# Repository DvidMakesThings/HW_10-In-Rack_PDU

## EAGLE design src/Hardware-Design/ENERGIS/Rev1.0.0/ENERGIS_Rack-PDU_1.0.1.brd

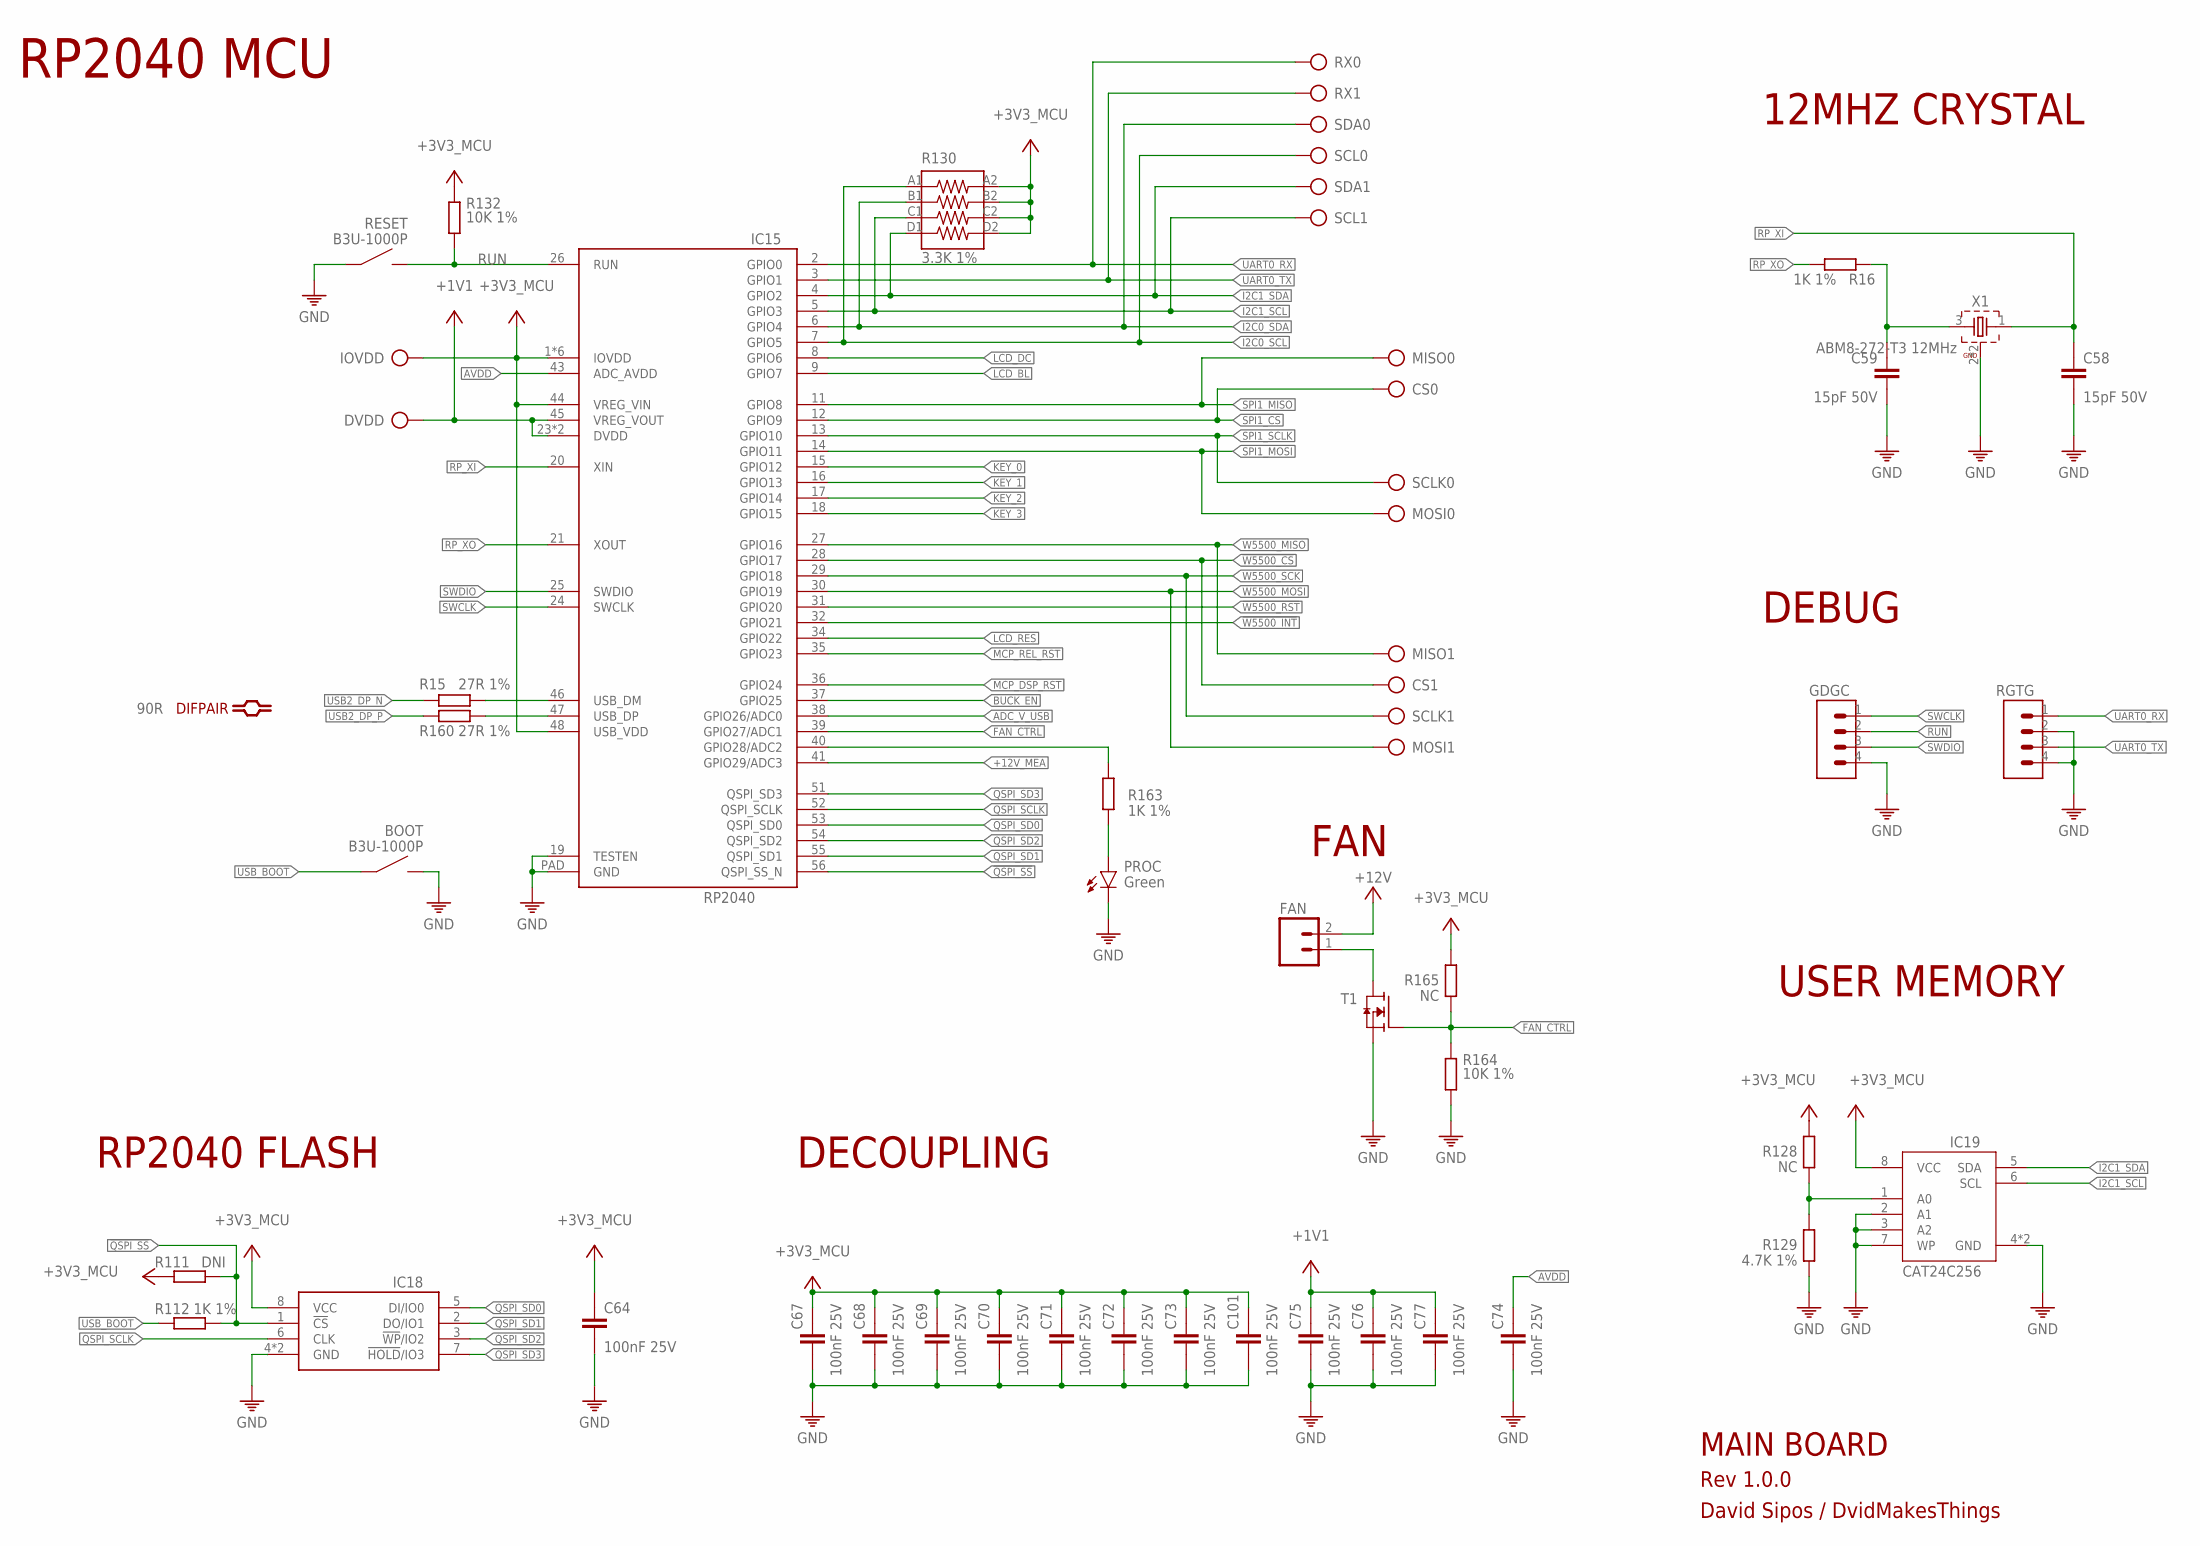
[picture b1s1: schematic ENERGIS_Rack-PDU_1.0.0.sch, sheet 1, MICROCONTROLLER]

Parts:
BOOT: B3U-1000P
C58, C59: 15pF 50V; 0201
C64, C67, C68, C69, C70, C71, C72, C73, C74, C75, C76, C77, C101: 100nF 25V; 0201
CS0, CS1: TP
DVDD: TP
FAN: M02; 02P
GDGC: CON-1X4; 1X4
IC15: RP2040; QFN56
IC18: W25Q128JVPIQ; SON127P600X500X75-8N
IC19: CAT24C256HU4IGT3; SON50P300X200X50-9T130X140N
IOVDD: TP
MISO0, MISO1: TP
MOSI0, MOSI1: TP
PROC: Green; LED-0603
R15, R160: 27R 1%; 0201
R16: 1K 1%; 0201
R111: DNI; R0201
R112, R163: 1K 1%; 0402
R128, R165: NC; R0201
R129: 4.7K 1%; 0201
R130: 3.3K 1%; _0603X4-1206
R132, R164: 10K 1%; 0402
RESET: B3U-1000P
RGTG: CON-1X4; 1X4
RX0, RX1: TP
SCL0, SCL1: TP
SCLK0, SCLK1: TP
SDA0, SDA1: TP
T1: BSS138; SOT23
X1: ABM8-272-T3 12MHz; WE-XTAL_CFPX-180

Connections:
!QSPI_SS: IC15.56 (QSPI_SS_N), IC18.1 (!CS), R111.1, R112.2
!W5500_CS: CS1.TP, IC15.28 (GPIO17); also elsewhere on the board
!W5500_INT: IC15.32 (GPIO21); also elsewhere on the board
!W5500_RST: IC15.31 (GPIO20); also elsewhere on the board
+1V1: C75.1, C76.1, C77.1, DVDD.TP, IC15.23 (DVDD), IC15.45 (VREG_VOUT), IC15.50 (DVDD)
+3V3_MCU: C64.1, C67.1, C68.1, C69.1, C70.1, C71.1, C72.1, C73.1, C101.1, IC15.1 (IOVDD), IC15.10 (IOVDD), IC15.22 (IOVDD), IC15.33 (IOVDD), IC15.42 (IOVDD), IC15.44 (VREG_VIN), IC15.48 (USB_VDD), IC15.49 (IOVDD), IC18.8 (VCC), IC19.8 (VCC), IOVDD.TP, R111.2, R128.2, R130.A2 (8), R130.B2 (7), R130.C2 (6), R130.D2 (5), R132.1, R165.2; also elsewhere on the board
+12V: FAN.2; also elsewhere on the board
+12V_MEA: IC15.41 (GPIO29/ADC3); also elsewhere on the board
ADC_V_USB: IC15.38 (GPIO26/ADC0); also elsewhere on the board
AVDD: C74.1, IC15.43 (ADC_AVDD); also elsewhere on the board
BUCK_EN: IC15.37 (GPIO25); also elsewhere on the board
FAN_CTRL: IC15.39 (GPIO27/ADC1), R164.1, R165.1, T1.1 (G)
GND: BOOT.2, C58.2, C59.2, C64.2, C67.2, C68.2, C69.2, C70.2, C71.2, C72.2, C73.2, C74.2, C75.2, C76.2, C77.2, C101.2, GDGC.4, IC15.19 (TESTEN), IC15.PAD (GND), IC18.4 (GND), IC18.PAD (GND), IC19.2 (A1), IC19.3 (A2), IC19.4 (GND), IC19.7 (WP), IC19.9 (GND), PROC.C, R129.1, R164.2, RESET.1, RGTG.2, RGTG.4, T1.2 (S), X1.2 (GND), X1.4 (GND); also elsewhere on the board
I2C0_SCL: IC15.7 (GPIO5), R130.A1 (1), SCL0.TP; also elsewhere on the board
I2C0_SDA: IC15.6 (GPIO4), R130.B1 (2), SDA0.TP; also elsewhere on the board
I2C1_SCL: IC15.5 (GPIO3), IC19.6 (SCL), R130.C1 (3), SCL1.TP; also elsewhere on the board
I2C1_SDA: IC15.4 (GPIO2), IC19.5 (SDA), R130.D1 (4), SDA1.TP; also elsewhere on the board
KEY_0: IC15.15 (GPIO12); also elsewhere on the board
KEY_1: IC15.16 (GPIO13); also elsewhere on the board
KEY_2: IC15.17 (GPIO14); also elsewhere on the board
KEY_3: IC15.18 (GPIO15); also elsewhere on the board
LCD_BL: IC15.9 (GPIO7); also elsewhere on the board
LCD_DC: IC15.8 (GPIO6); also elsewhere on the board
LCD_RES: IC15.34 (GPIO22); also elsewhere on the board
MCP_DSP_RST: IC15.36 (GPIO24); also elsewhere on the board
MCP_REL_RST: IC15.35 (GPIO23); also elsewhere on the board
unnamed: IC15.40 (GPIO28/ADC2), R163.2
unnamed: PROC.A, R163.1
unnamed: FAN.1, T1.3 (D)
unnamed: C59.1, R16.1, X1.3 (2)
unnamed: IC19.1 (A0), R128.1, R129.2
QSPI_SCLK: IC15.52 (QSPI_SCLK), IC18.6 (CLK)
QSPI_SD0: IC15.53 (QSPI_SD0), IC18.5 (DI/IO0)
QSPI_SD1: IC15.55 (QSPI_SD1), IC18.2 (DO/IO1)
QSPI_SD2: IC15.54 (QSPI_SD2), IC18.3 (!WP!/IO2)
QSPI_SD3: IC15.51 (QSPI_SD3), IC18.7 (!HOLD!/IO3)
RP_DP_N: IC15.46 (USB_DM), R15.2
RP_DP_P: IC15.47 (USB_DP), R160.2
RP_XI: C58.1, IC15.20 (XIN), X1.1
RP_XO: IC15.21 (XOUT), R16.2
RUN: GDGC.2, IC15.26 (RUN), R132.2, RESET.2
SPI1_CS: CS0.TP, IC15.12 (GPIO9); also elsewhere on the board
SPI1_MISO: IC15.11 (GPIO8), MISO0.TP; also elsewhere on the board
SPI1_MOSI: IC15.14 (GPIO11), MOSI0.TP; also elsewhere on the board
SPI1_SCLK: IC15.13 (GPIO10), SCLK0.TP; also elsewhere on the board
SWCLK: GDGC.1, IC15.24 (SWCLK)
SWDIO: GDGC.3, IC15.25 (SWDIO)
UART0_RX: IC15.2 (GPIO0), RGTG.1, RX0.TP; also elsewhere on the board
UART0_TX: IC15.3 (GPIO1), RGTG.3, RX1.TP; also elsewhere on the board
USB2_DP_N: R15.1; also elsewhere on the board
USB2_DP_P: R160.1; also elsewhere on the board
USB_BOOT: BOOT.1, R112.1
W5500_MISO: IC15.27 (GPIO16), MISO1.TP; also elsewhere on the board
W5500_MOSI: IC15.30 (GPIO19), MOSI1.TP; also elsewhere on the board
W5500_SCK: IC15.29 (GPIO18), SCLK1.TP; also elsewhere on the board

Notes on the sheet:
DECOUPLING
12MHZ CRYSTAL
RP2040 MCU
RP2040 FLASH
USER MEMORY
DEBUG
MAIN BOARD
Rev 1.0.0
David Sipos / DvidMakesThings
FAN

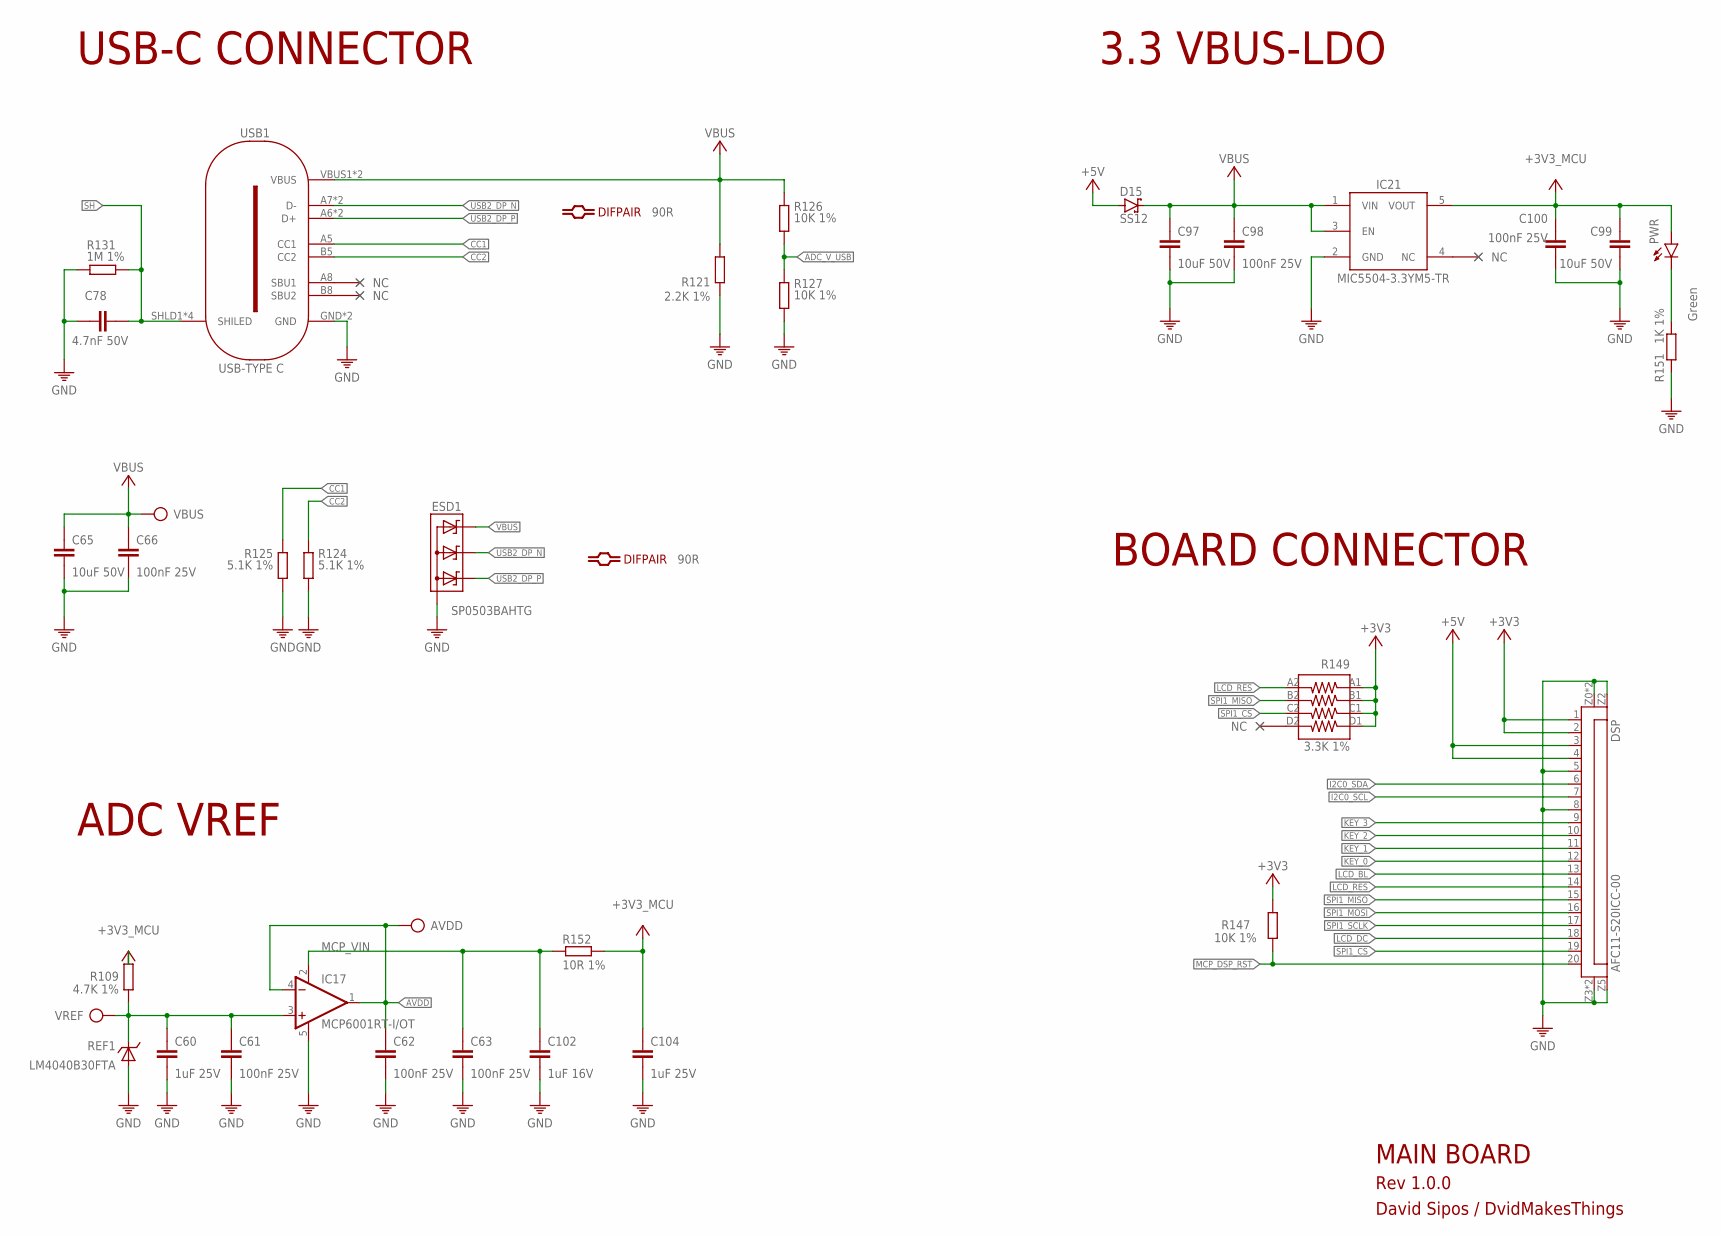
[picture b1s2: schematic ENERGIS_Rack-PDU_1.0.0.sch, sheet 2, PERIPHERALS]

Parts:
AVDD: TP
C60, C104: 1uF 25V; 0402
C61, C62, C63, C98, C100: 100nF 25V; 0201
C65, C97, C99: 10uF 50V; 0805
C66: 100nF 25V; 0402
C78: 4.7nF 50V; 0402
C102: 1uF 16V; 0201
D15: SS12; SMA/DO-214AC
DSP: AFC11-S20ICC-00; FPC20
ESD1: SP0503BAHTG; SOT143
IC17: MCP6001RT-I/OT; SOT23-5
IC21: MIC5504-3.3YM5; SOT23-5
PWR: Green; LED-0603
R109: 4.7K 1%; 0201
R121: 2.2K 1%; 0201
R124, R125: 5.1K 1%; 0201
R126, R127: 10K 1%; 0201
R131: 1M 1%; 0402
R147: 10K 1%; 0402
R149: 3.3K 1%; _0603X4-1206
R151: 1K 1%; 0402
R152: 10R 1%; 0201
REF1: LM4040B30FTA; SOT23
USB1: USB-TYPE-C-018; USB-C
VBUS: TP
VREF: TP

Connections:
+3V3: DSP.1, DSP.2, R147.2, R149.A1 (1), R149.B1 (2), R149.C1 (3), R149.D1 (4); also elsewhere on the board
+3V3_MCU: C99.1, C100.1, C104.1, IC21.5 (VOUT), PWR.A, R109.2, R152.1; also elsewhere on the board
+5V: D15.A, DSP.3, DSP.4; also elsewhere on the board
ADC_V_USB: R126.2, R127.1; also elsewhere on the board
AVDD: AVDD.TP, C62.1, IC17.1 (OUT), IC17.4 (-IN); also elsewhere on the board
CC1: R125.1, USB1.A5 (CC1)
CC2: R124.1, USB1.B5 (CC2)
GND: C60.2, C61.2, C62.2, C63.2, C65.2, C66.2, C78.2, C97.2, C98.2, C99.2, C100.2, C102.2, C104.2, DSP.5, DSP.8, DSP.Z0 (Z1), DSP.Z1, DSP.Z2, DSP.Z3, DSP.Z4 (Z3), DSP.Z5 (Z4), ESD1.1 (A), IC17.5 (V-), IC21.2 (GND), R121.2, R124.2, R125.2, R127.2, R131.2, R151.1, REF1.2 (A), REF1.3 (A), USB1.GND, USB1.GND2 (GND); also elsewhere on the board
I2C0_SCL: DSP.7; also elsewhere on the board
I2C0_SDA: DSP.6; also elsewhere on the board
KEY_0: DSP.12; also elsewhere on the board
KEY_1: DSP.11; also elsewhere on the board
KEY_2: DSP.10; also elsewhere on the board
KEY_3: DSP.9; also elsewhere on the board
LCD_BL: DSP.13; also elsewhere on the board
LCD_DC: DSP.18; also elsewhere on the board
LCD_RES: DSP.14, R149.A2 (8); also elsewhere on the board
MCP_DSP_RST: DSP.20, R147.1; also elsewhere on the board
MCP_VIN: C63.1, C102.1, IC17.2 (V+), R152.2
unnamed: PWR.C, R151.2
SH: C78.1, R131.1, USB1.SHLD1 (SHILED), USB1.SHLD2 (SHILED), USB1.SHLD3 (SHILED), USB1.SHLD4 (SHILED); also elsewhere on the board
SPI1_CS: DSP.19, R149.C2 (6); also elsewhere on the board
SPI1_MISO: DSP.15, R149.B2 (7); also elsewhere on the board
SPI1_MOSI: DSP.16; also elsewhere on the board
SPI1_SCLK: DSP.17; also elsewhere on the board
USB2_DP_N: ESD1.3 (C2), USB1.A7 (D-), USB1.B7 (D-); also elsewhere on the board
USB2_DP_P: ESD1.2 (C1), USB1.A6 (D+), USB1.B6 (D+); also elsewhere on the board
VBUS: C65.1, C66.1, C97.1, C98.1, D15.C, ESD1.4 (C3), IC21.1 (VIN), IC21.3 (EN), R121.1, R126.1, USB1.VBUS1 (VBUS), USB1.VBUS2 (VBUS), VBUS.TP
VREF: C60.1, C61.1, IC17.3 (+IN), R109.1, REF1.1 (C), VREF.TP

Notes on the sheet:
MAIN BOARD
Rev 1.0.0
David Sipos / DvidMakesThings
USB-C CONNECTOR
ADC VREF
3.3 VBUS-LDO
BOARD CONNECTOR

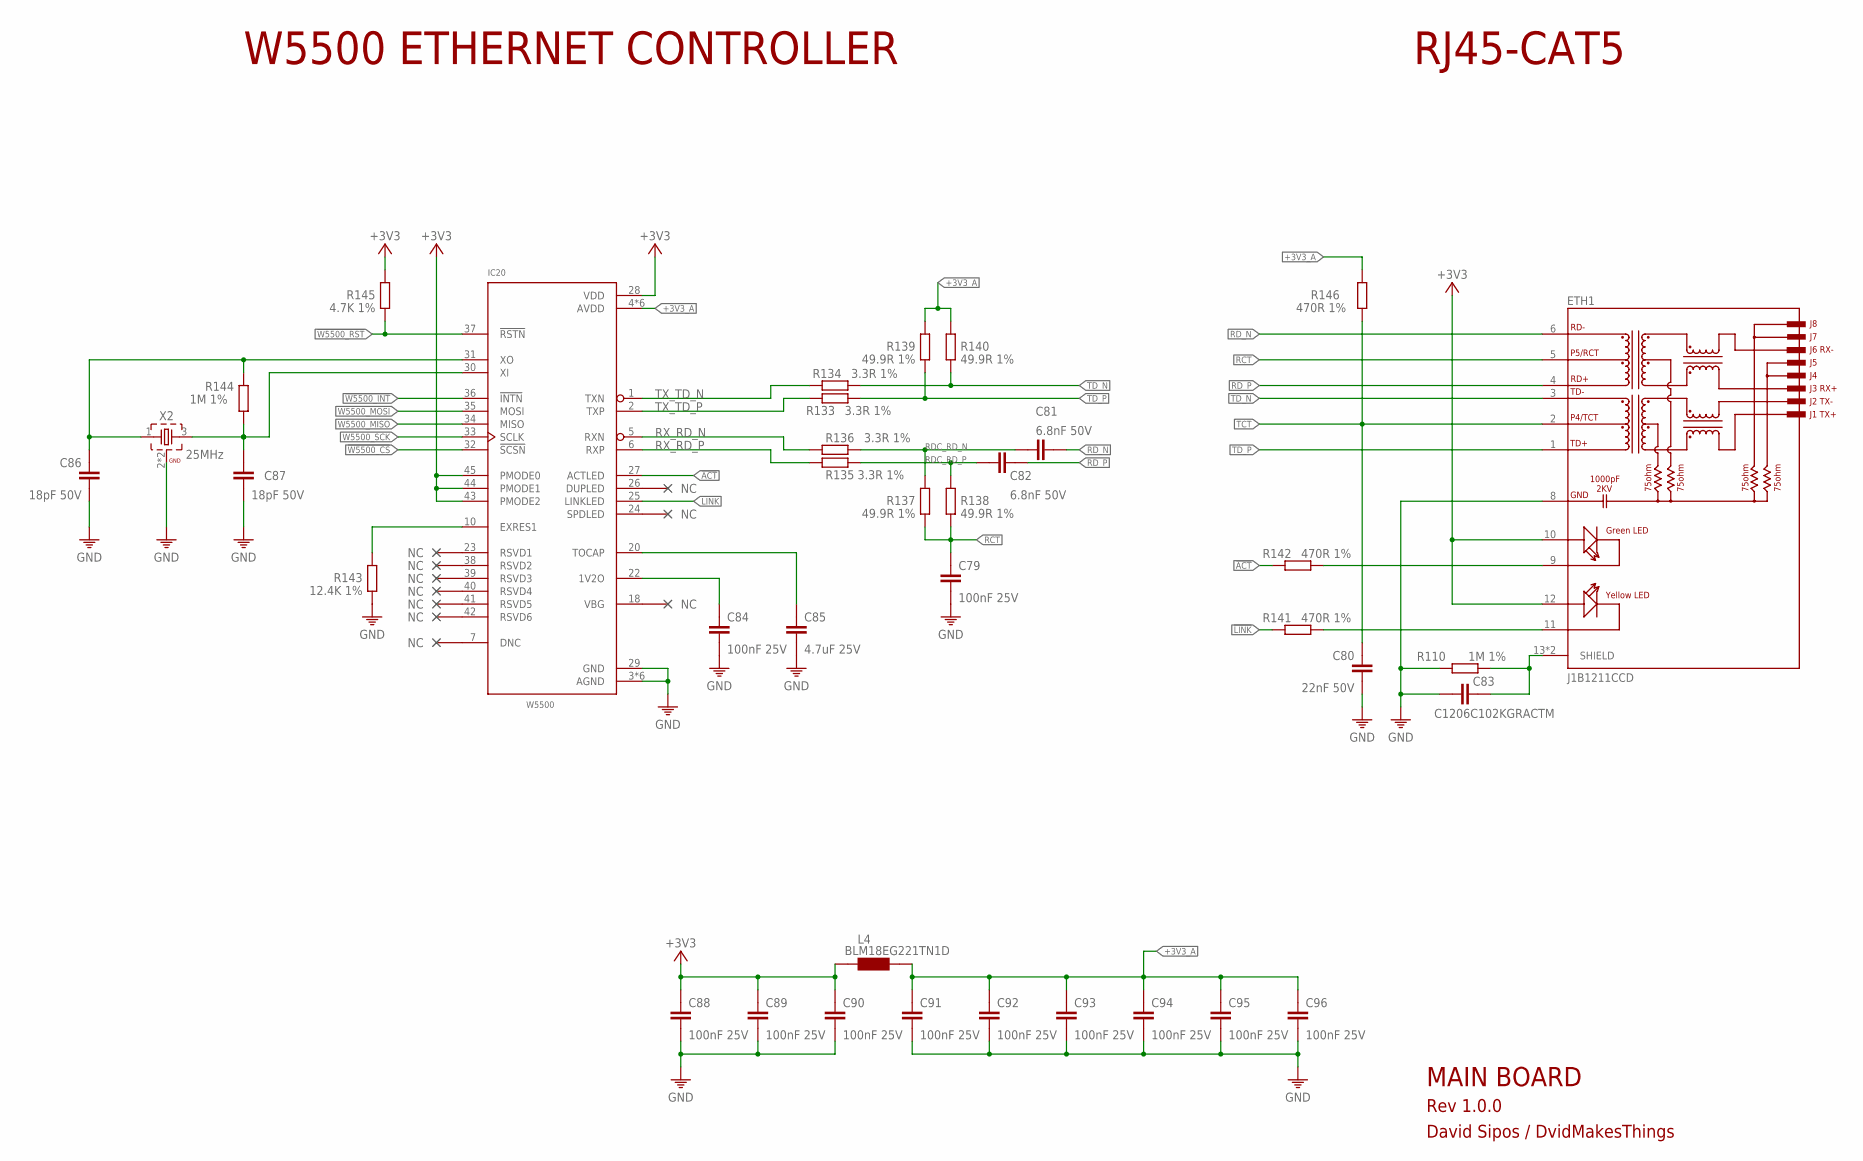
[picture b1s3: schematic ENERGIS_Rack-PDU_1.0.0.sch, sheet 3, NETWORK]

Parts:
C79: 100nF 25V; 0402
C80: 22nF 50V; 0402
C81, C82: 6.8nF 50V; 0201
C83: C1206C102KGRACTM; C1206
C84, C88, C89, C90, C91, C92, C93, C94, C95, C96: 100nF 25V; 0201
C85: 4.7uF 25V; 0402
C86, C87: 18pF 50V; 0201
ETH1: J1B1211CCD
IC20: W5500; LQFP48
L4: BLM18EG221TN1D; 0603
R110: 1M 1%; 1206
R133, R134, R135, R136: 3.3R 1%; 0201
R137, R138, R139, R140: 49.9R 1%; 0201
R141, R142, R146: 470R 1%; 0402
R143: 12.4K 1%; R0201
R144: 1M 1%; 0201
R145: 4.7K 1%; 0201
X2: 25MHz; WE-XTAL_CFPX-180

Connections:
!ACT: IC20.27 (ACTLED), R142.1
!LINK: IC20.25 (LINKLED), R141.1
!W5500_CS: IC20.32 (!SCSN); also elsewhere on the board
!W5500_INT: IC20.36 (!INTN); also elsewhere on the board
!W5500_RST: IC20.37 (!RSTN), R145.1; also elsewhere on the board
+3V3: C88.1, C89.1, C90.1, ETH1.10 (GREEN+), ETH1.12 (YELLOW+), IC20.28 (VDD), IC20.43 (PMODE2), IC20.44 (PMODE1), IC20.45 (PMODE0), L4.1, R145.2; also elsewhere on the board
+3V3_A: C91.1, C92.1, C93.1, C94.1, C95.1, C96.1, IC20.4 (AVDD), IC20.8 (AVDD), IC20.11 (AVDD), IC20.15 (AVDD), IC20.17 (AVDD), IC20.21 (AVDD), L4.2, R139.2, R140.2, R146.2
GND: C79.2, C80.2, C83.1, C84.2, C85.2, C86.2, C87.2, C88.2, C89.2, C90.2, C91.2, C92.2, C93.2, C94.2, C95.2, C96.2, ETH1.8 (GND), IC20.3 (AGND), IC20.9 (AGND), IC20.14 (AGND), IC20.16 (AGND), IC20.19 (AGND), IC20.29 (GND), IC20.48 (AGND), R110.1, R143.1, X2.2 (GND), X2.4 (GND); also elsewhere on the board
unnamed: ETH1.11 (YELLOW-), R141.2
unnamed: ETH1.9 (GREEN-), R142.2
unnamed: IC20.10 (EXRES1), R143.2
unnamed: C84.1, IC20.22 (1V2O)
unnamed: C85.1, IC20.20 (TOCAP)
unnamed: C87.1, IC20.30 (XI), R144.1, X2.3 (2)
RCT: C79.1, ETH1.5 (P5/RCT), R137.1, R138.1
RDC_RD_N: C81.1, R136.2, R137.2
RDC_RD_P: C82.1, R135.2, R138.2
RD_N: C81.2, ETH1.6 (RD-)
RD_P: C82.2, ETH1.4 (RD+)
RX_RD_N: IC20.5 (RXN), R136.1
RX_RD_P: IC20.6 (RXP), R135.1
SH: C83.2, ETH1.13 (SHIELD), ETH1.14 (SHIELD), R110.2; also elsewhere on the board
TCT: C80.1, ETH1.2 (P4/TCT), R146.1
TD_N: ETH1.3 (TD-), R134.2, R140.1
TD_P: ETH1.1 (TD+), R133.2, R139.1
TX_TD_N: IC20.1 (TXN), R134.1
TX_TD_P: IC20.2 (TXP), R133.1
W5500_MISO: IC20.34 (MISO); also elsewhere on the board
W5500_MOSI: IC20.35 (MOSI); also elsewhere on the board
W5500_SCK: IC20.33 (SCLK); also elsewhere on the board
XO: C86.1, IC20.31 (XO), R144.2, X2.1

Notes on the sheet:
W5500 ETHERNET CONTROLLER
RJ45-CAT5
MAIN BOARD
Rev 1.0.0
David Sipos / DvidMakesThings

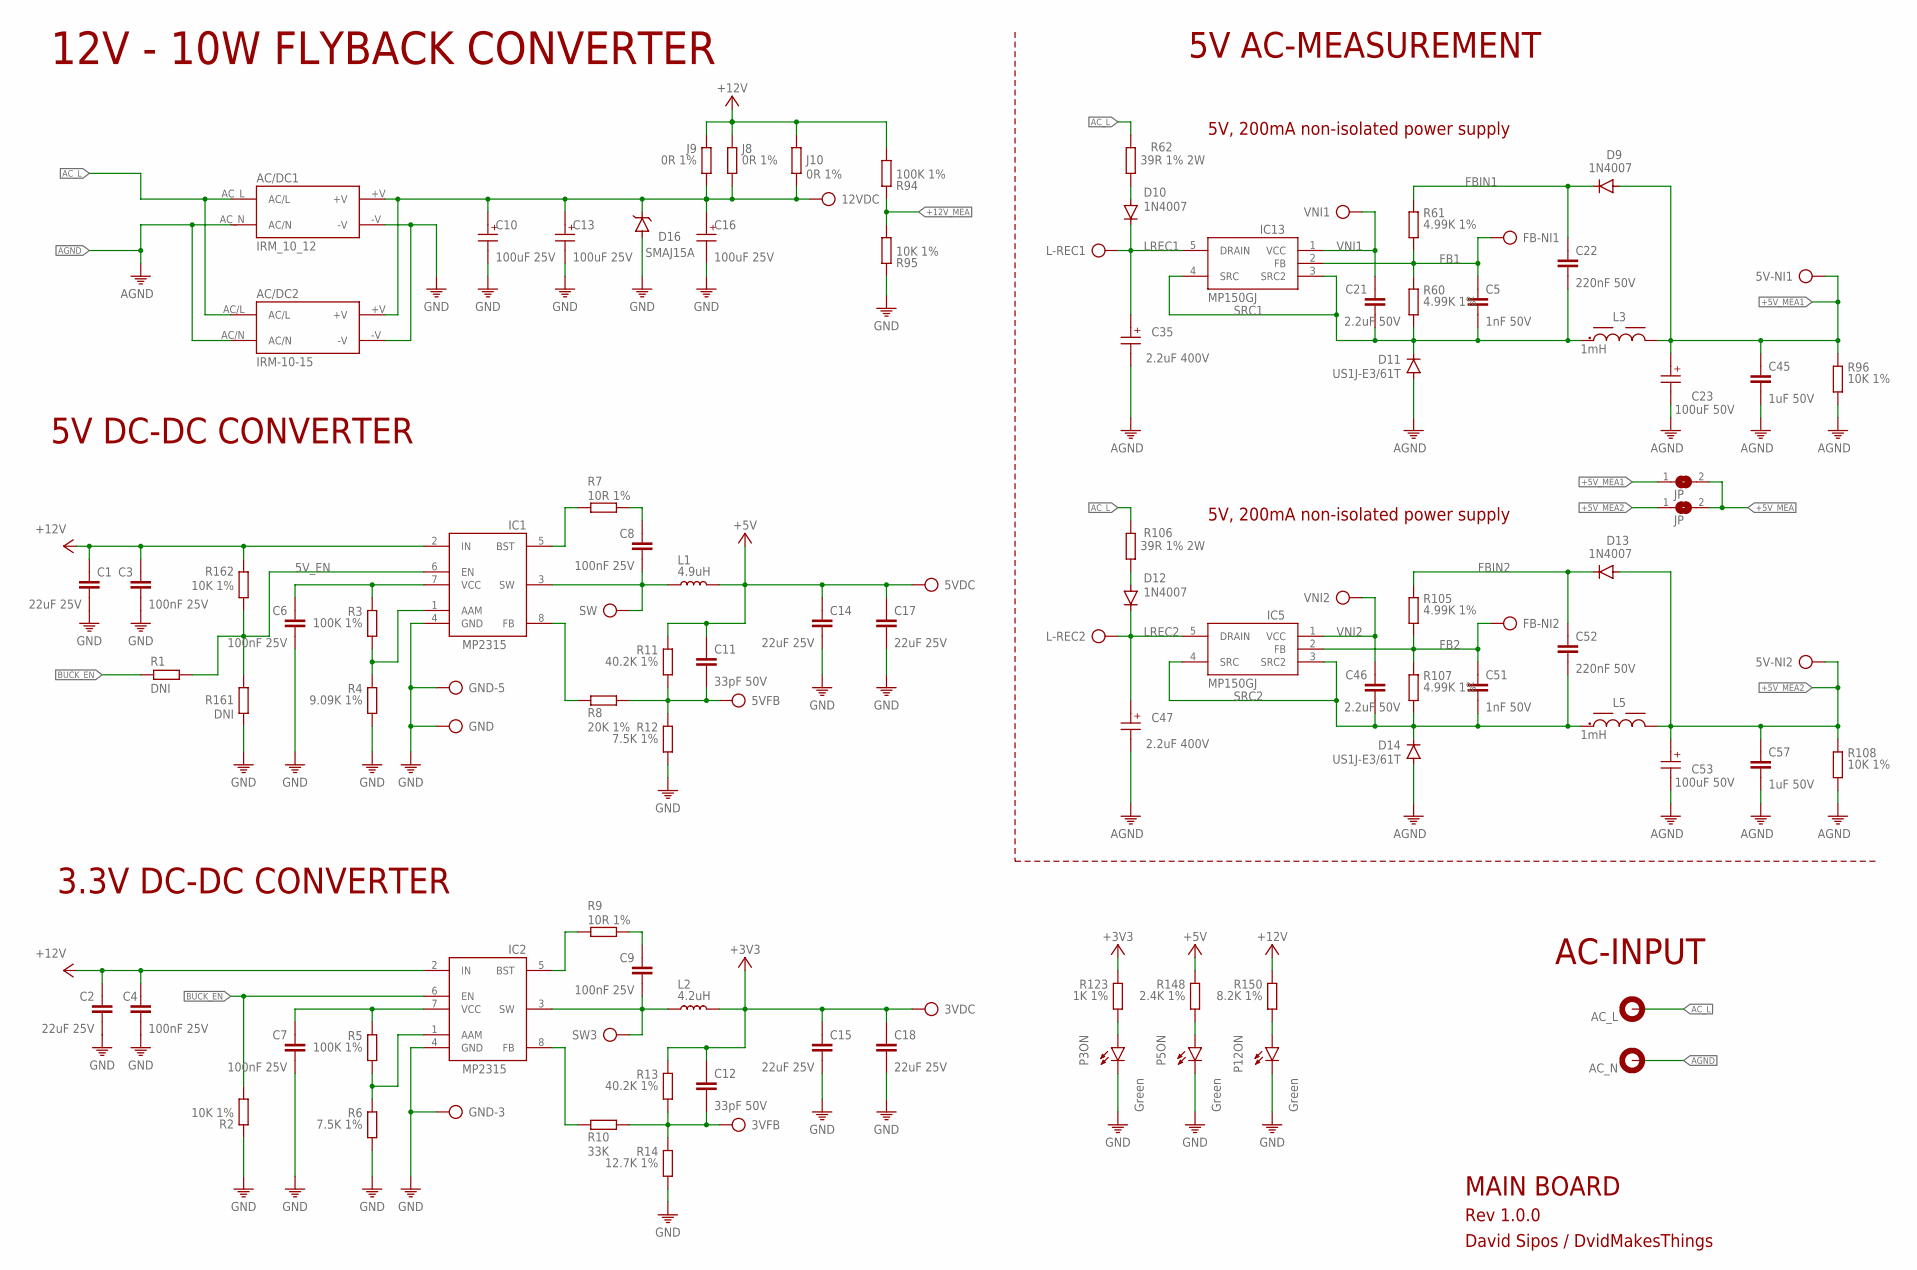
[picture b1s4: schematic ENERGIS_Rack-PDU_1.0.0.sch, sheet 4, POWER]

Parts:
3VDC, 3VFB, 5V-NI1, 5V-NI2, 5VDC, 5VFB, 12VDC: TP
AC/DC1: IRM_10_12
AC/DC2: IRM-10-15; IRM_15_12
AC_L: MOUNT-PAD-ROUND3.0; 3,0-PAD
AC_N: MOUNT-PAD-ROUND3.0; 3,0-PAD
C1, C2, C14, C15, C17, C18: 22uF 25V; 1206
C3, C4, C6, C7, C8, C9: 100nF 25V; 0402
C5, C51: 1nF 50V; 0603
C10, C13, C16: 100uF 25V; 6.3X7.7(DXL)
C11, C12: 33pF 50V; 0402
C21, C46: 2.2uF 50V; 0603
C22, C52: 220nF 50V; 0805
C23, C53: 100uF 50V; 6.3X7.7(DXL)
C35, C47: 2.2uF 400V; 6.3X7.7(DXL)
C45, C57: 1uF 50V; 0805
D9, D10, D12, D13: 1N4007; SMA/DO-214AC
D11, D14: US1J-E3/61T; SMA/DO-214AC
D16: SMAJ15A; SMA/DO-214AC
FB-NI1, FB-NI2: TP
GND: TP
GND-3, GND-5: TP
IC1, IC2: MP2315GJ-Z; SOT65P280X110-8N
IC5, IC13: MP150GJ; SOT23-5
J2, J7: JP; SJ
J8, J9, J10: 0R 1%; 0805
L1: 4.9uH; SRR5228A
L2: 4.2uH; SRR5228A
L3, L5: 1mH; L-6.6X6.6
L-REC1, L-REC2: TP
P3ON, P5ON, P12ON: Green; LED-0603
R1, R161: DNI; 0402
R2, R95, R162: 10K 1%; 0402
R3, R5, R94: 100K 1%; 0402
R4: 9.09K 1%; 0402
R6, R12: 7.5K 1%; 0402
R7, R9: 10R 1%; 0402
R8: 20K 1%; 0402
R10: 33K; 0402
R11, R13: 40.2K 1%; 0402
R14: 12.7K 1%; 0402
R60, R61, R105, R107: 4.99K 1%; 0603
R62, R106: 39R 1% 2W; 2512
R96, R108: 10K 1%; 0805
R123: 1K 1%; 0402
R148: 2.4K 1%; 0402
R150: 8.2K 1%; 0402
SW, SW3: TP
VNI1, VNI2: TP

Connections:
3VFB: 3VFB.TP, C12.2, R10.2, R13.2, R14.1
5VFB: 5VFB.TP, C11.2, R8.2, R11.2, R12.1
5V_EN: IC1.6 (EN), R1.1, R161.2, R162.1
12VRAW: 12VDC.TP, AC/DC1.+V, AC/DC2.+V, C10.1 (+), C13.1 (+), C16.1 (+), D16.C, J8.2, J9.2, J10.2
+3V3: 3VDC.TP, C12.1, C15.1, C18.1, L2.2, R13.1, R123.1; also elsewhere on the board
+5V: 5VDC.TP, C11.1, C14.1, C17.1, L1.2, R11.1, R148.1; also elsewhere on the board
+5V_MEA: J2.2, J7.2; also elsewhere on the board
+5V_MEA1: 5V-NI1.TP, C23.1 (+), C45.2, D9.A, J2.1, L3.2, R96.1
+5V_MEA2: 5V-NI2.TP, C53.1 (+), C57.2, D13.A, J7.1, L5.2, R108.1
+12V: C1.1, C2.1, C3.1, C4.1, IC1.2 (IN), IC2.2 (IN), J8.1, J9.1, J10.1, R94.2, R150.1, R162.2; also elsewhere on the board
+12V_MEA: R94.1, R95.2; also elsewhere on the board
AC_L: AC/DC1.AC_L (AC/L), AC/DC2.AC/L, AC_L.B3,0, R62.1, R106.1; also elsewhere on the board
AGND: AC/DC1.AC_N (AC/N), AC/DC2.AC/N, AC_N.B3,0, C23.2 (-), C35.2 (-), C45.1, C47.2 (-), C53.2 (-), C57.1, D11.A, D14.A, R96.2, R108.2; also elsewhere on the board
BUCK_EN: IC2.6 (EN), R1.2, R2.2; also elsewhere on the board
FB1: C5.2, FB-NI1.TP, IC13.2 (FB), R60.1, R61.2
FB2: C51.2, FB-NI2.TP, IC5.2 (FB), R105.2, R107.1
FBIN1: C22.2, D9.C, R61.1
FBIN2: C52.2, D13.C, R105.1
GND: AC/DC1.-V, AC/DC2.-V, C1.2, C2.2, C3.2, C4.2, C6.2, C7.2, C10.2 (-), C13.2 (-), C14.2, C15.2, C16.2 (-), C17.2, C18.2, D16.A, GND.TP, GND-3.TP, GND-5.TP, IC1.4 (GND), IC2.4 (GND), P3ON.C, P5ON.C, P12ON.C, R2.1, R4.2, R6.2, R12.2, R14.2, R95.1, R161.1; also elsewhere on the board
LREC1: C35.1 (+), D10.C, IC13.5 (DRAIN), L-REC1.TP
LREC2: C47.1 (+), D12.C, IC5.5 (DRAIN), L-REC2.TP
unnamed: P3ON.A, R123.2
unnamed: D10.A, R62.2
unnamed: P5ON.A, R148.2
unnamed: P12ON.A, R150.2
unnamed: IC1.5 (BST), R7.2
unnamed: IC1.8 (FB), R8.1
unnamed: C8.1, R7.1
unnamed: C6.1, IC1.7 (VCC), R3.1
unnamed: IC2.5 (BST), R9.2
unnamed: IC2.8 (FB), R10.1
unnamed: C9.1, R9.1
unnamed: C7.1, IC2.7 (VCC), R5.1
unnamed: IC1.1 (AAM), R3.2, R4.1
unnamed: IC2.1 (AAM), R5.2, R6.1
unnamed: D12.A, R106.2
SRC1: C5.1, C21.1, C22.1, D11.C, IC13.3 (SRC2), IC13.4 (SRC), L3.1, R60.2
SRC2: C46.1, C51.1, C52.1, D14.C, IC5.3 (SRC2), IC5.4 (SRC), L5.1, R107.2
SW3: C9.2, IC2.3 (SW), L2.1, SW3.TP
SW5: C8.2, IC1.3 (SW), L1.1, SW.TP
VNI1: C21.2, IC13.1 (VCC), VNI1.TP
VNI2: C46.2, IC5.1 (VCC), VNI2.TP

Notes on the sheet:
12V - 10W FLYBACK CONVERTER
5V DC-DC CONVERTER
3.3V DC-DC CONVERTER
5V AC-MEASUREMENT
AC-INPUT
5V, 200mA non-isolated power supply
MAIN BOARD
Rev 1.0.0
David Sipos / DvidMakesThings

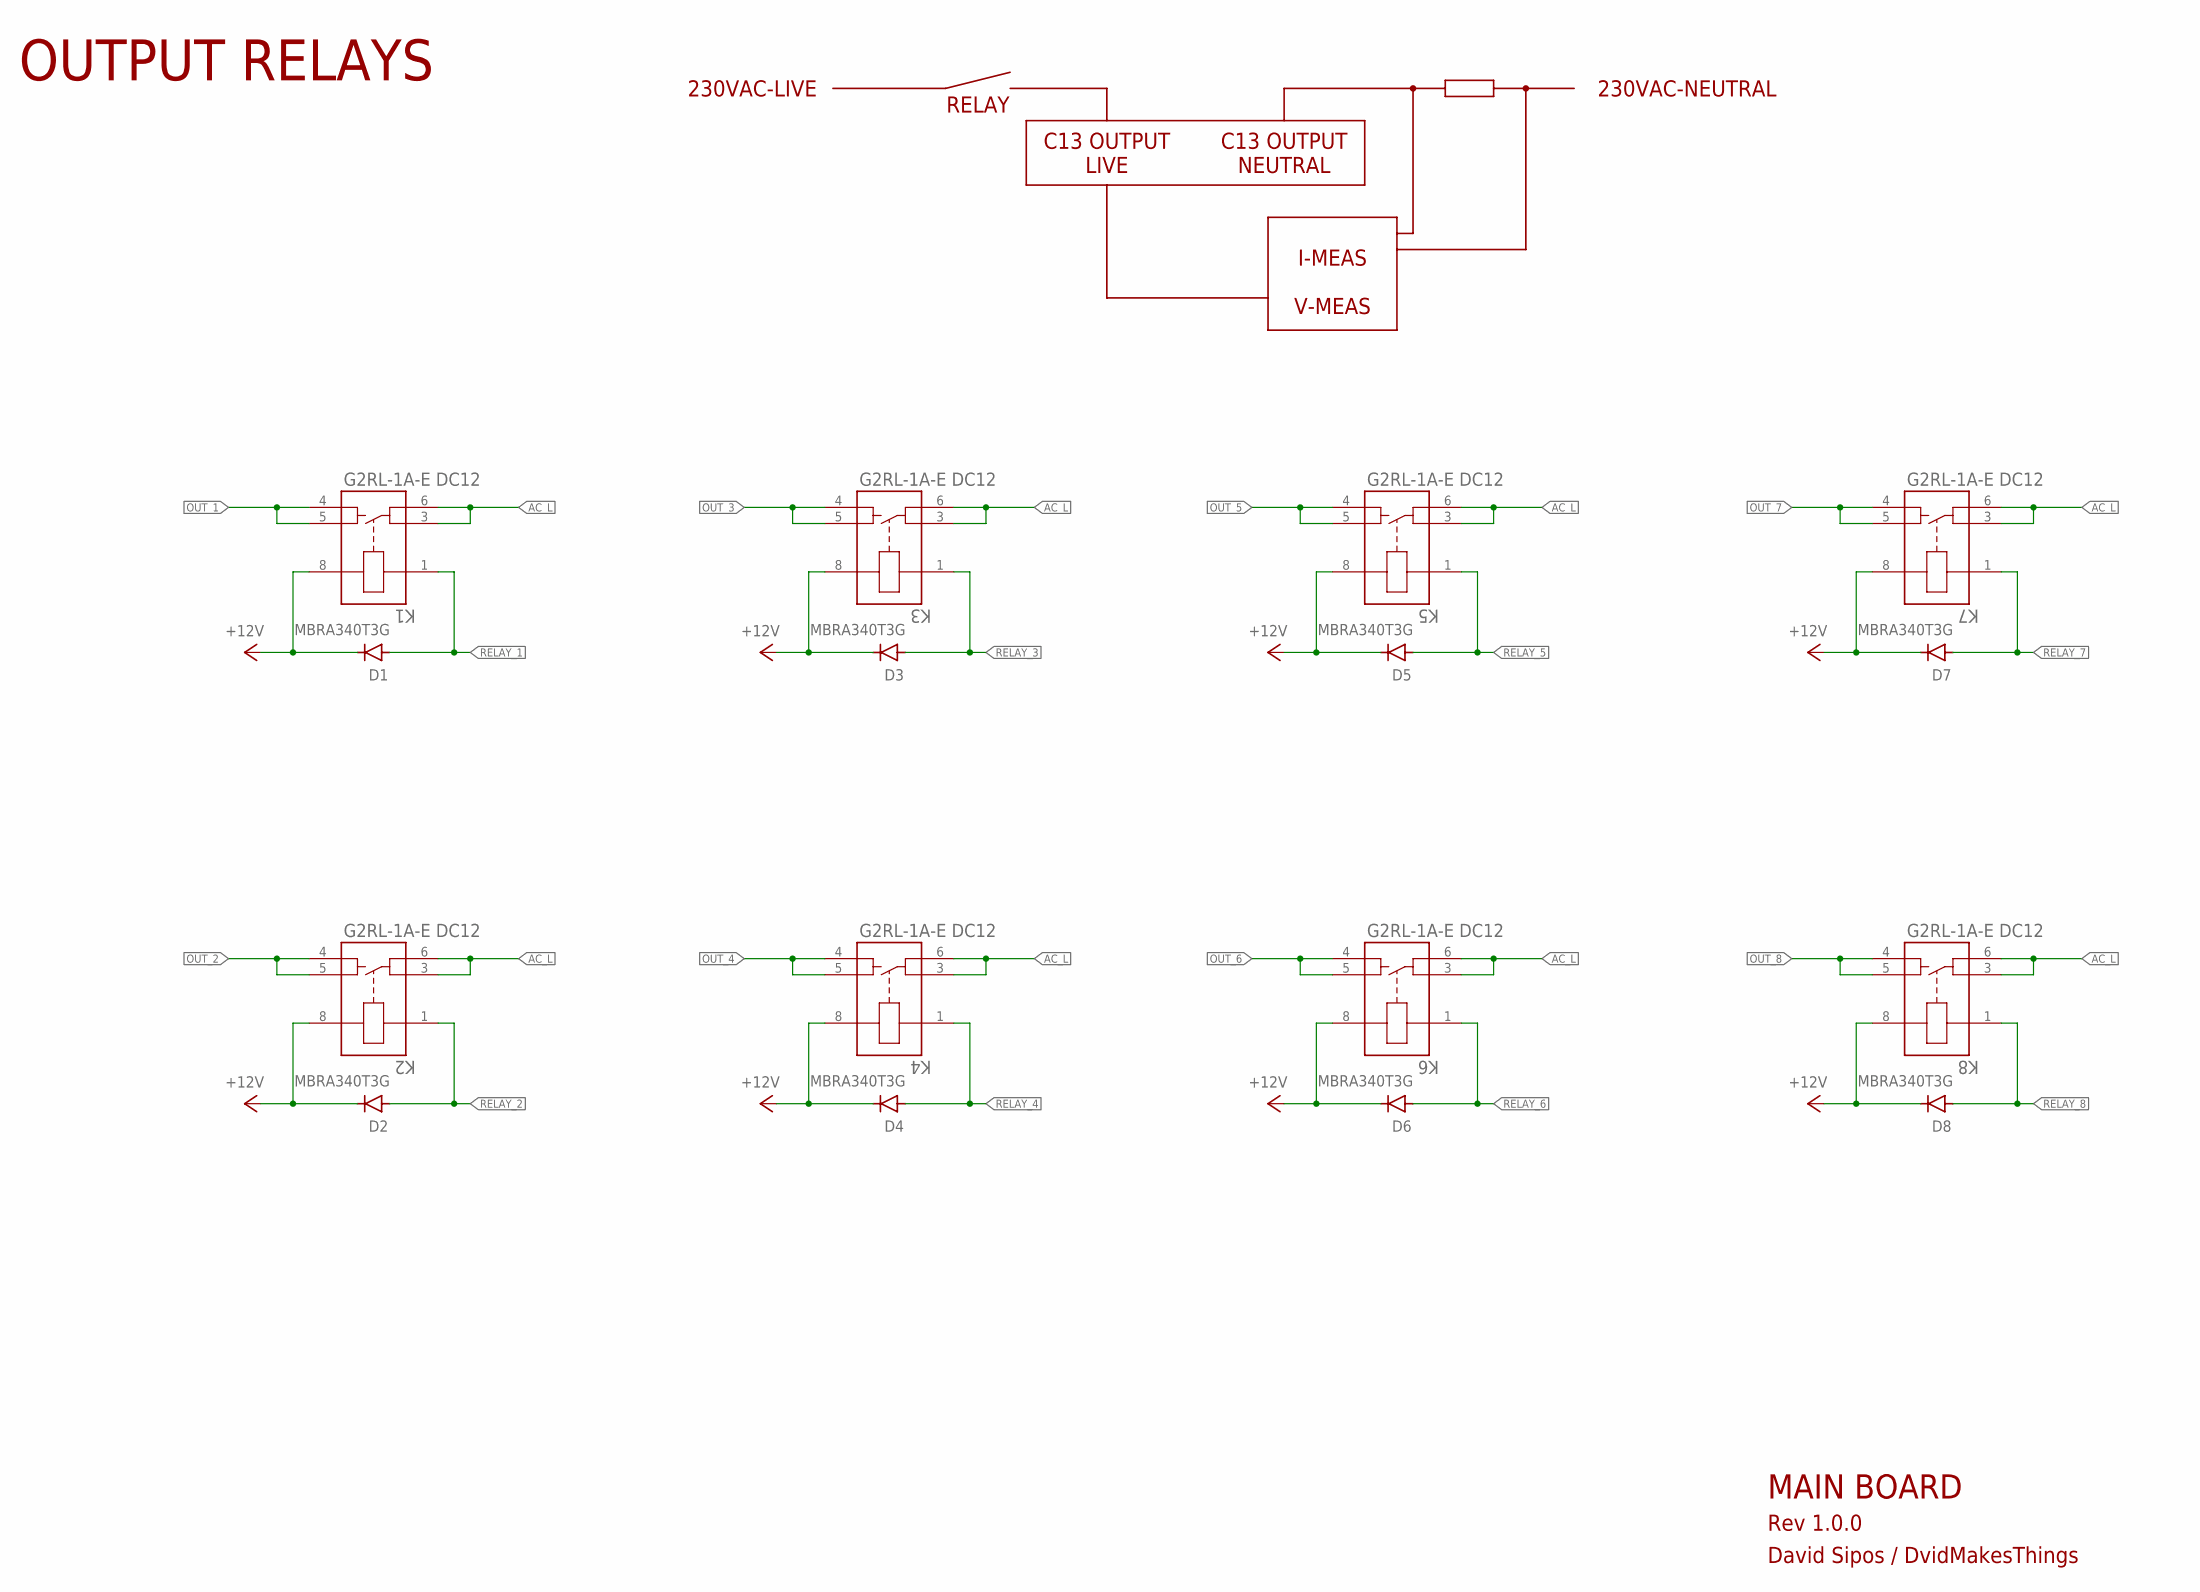
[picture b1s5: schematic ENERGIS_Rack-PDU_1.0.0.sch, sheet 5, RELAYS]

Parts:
D1, D2, D3, D4, D5, D6, D7, D8: MBRA340T3G; SMA/DO-214AC
K1, K2, K3, K4, K5, K6, K7, K8: G2RL-1A-E DC12; RELAY_G2RL-1A-E_DC5_OMR

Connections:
+12V: D1.C, D2.C, D3.C, D4.C, D5.C, D6.C, D7.C, D8.C, K1.8, K2.8, K3.8, K4.8, K5.8, K6.8, K7.8, K8.8; also elsewhere on the board
AC_L: K1.3, K1.6, K2.3, K2.6, K3.3, K3.6, K4.3, K4.6, K5.3, K5.6, K6.3, K6.6, K7.3, K7.6, K8.3, K8.6; also elsewhere on the board
OUT_1: K1.4, K1.5; also elsewhere on the board
OUT_2: K2.4, K2.5; also elsewhere on the board
OUT_3: K3.4, K3.5; also elsewhere on the board
OUT_4: K4.4, K4.5; also elsewhere on the board
OUT_5: K5.4, K5.5; also elsewhere on the board
OUT_6: K6.4, K6.5; also elsewhere on the board
OUT_7: K7.4, K7.5; also elsewhere on the board
OUT_8: K8.4, K8.5; also elsewhere on the board
RELAY_1: D1.A, K1.1; also elsewhere on the board
RELAY_2: D2.A, K2.1; also elsewhere on the board
RELAY_3: D3.A, K3.1; also elsewhere on the board
RELAY_4: D4.A, K4.1; also elsewhere on the board
RELAY_5: D5.A, K5.1; also elsewhere on the board
RELAY_6: D6.A, K6.1; also elsewhere on the board
RELAY_7: D7.A, K7.1; also elsewhere on the board
RELAY_8: D8.A, K8.1; also elsewhere on the board

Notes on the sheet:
OUTPUT RELAYS
MAIN BOARD
Rev 1.0.0
David Sipos / DvidMakesThings
230VAC-LIVE
C13 OUTPUT NEUTRAL
C13 OUTPUT LIVE
RELAY
230VAC-NEUTRAL
I-MEAS V-MEAS

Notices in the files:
parts and their libraries:
ds_trafo: Copyright: Würth Elektronik
SparkFun-Aesthetics: Licensing: Creative Commons ShareAlike 4.0 International - https://creativecommons.org/licenses/by-sa/4.0
ds_passive: COPYRIGHT: Copyright (C) 2025 Ultra Librarian. All rights reserved.
crystal-geyer_V1_0: Copyright: Geyer-Electronic
